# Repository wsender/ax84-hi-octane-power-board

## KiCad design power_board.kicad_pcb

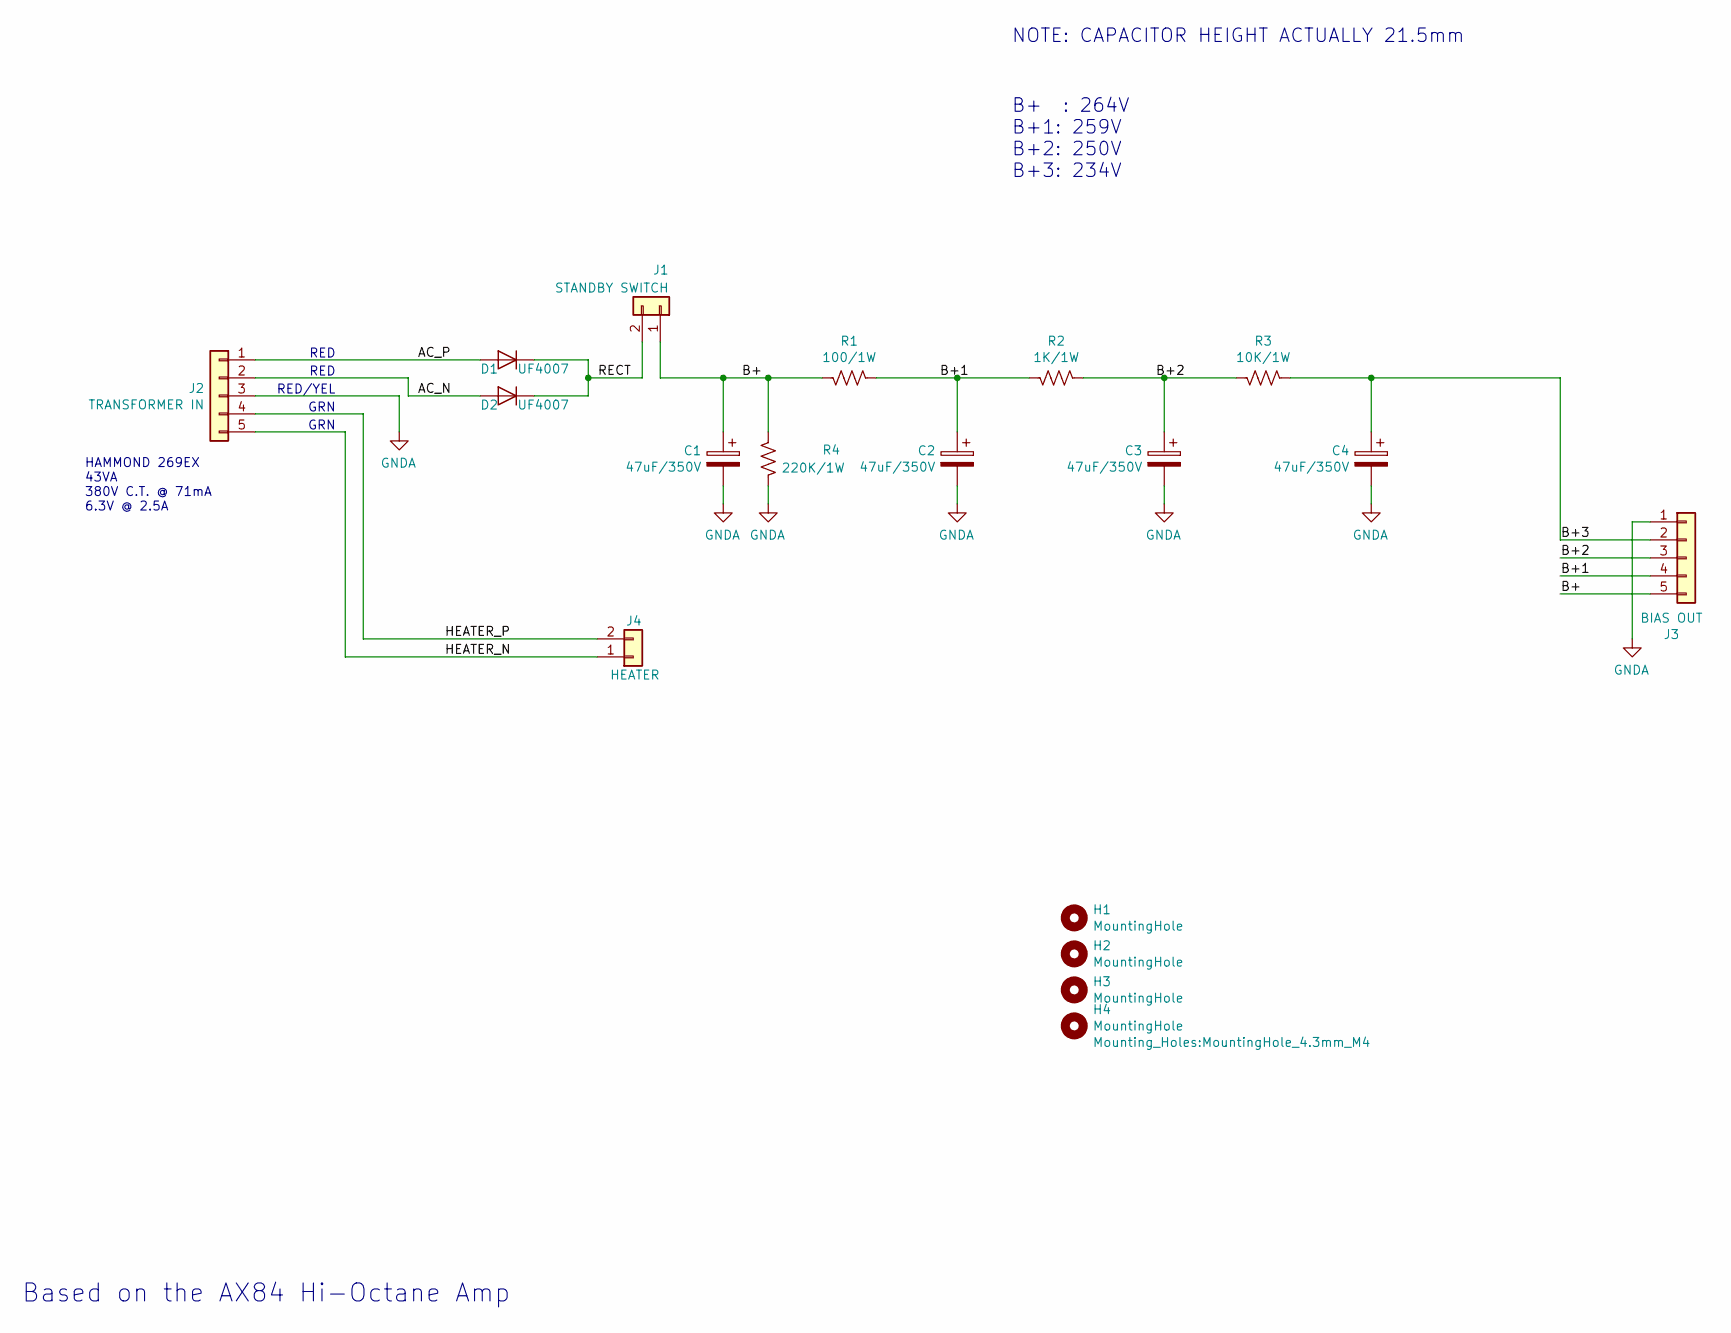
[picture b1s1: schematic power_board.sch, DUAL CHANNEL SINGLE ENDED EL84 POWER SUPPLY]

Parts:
C1, C2, C3, C4: 47uF/350V; CP_Radial_D16.0mm_P7.50mm; DIGIKEY PN 493-14944-ND
D1, D2: UF4007; D_DO-41_SOD81_P10.16mm_Horizontal; DIGIKEY PN UF4007-E3/54GICT-ND
H1, H2, H3, H4: MountingHole; MountingHole_4.3mm_M4
J1: STANDBY SWITCH; TerminalBlock_Pheonix_PT-3.5mm_2pol; DIGIKEY PN 277-6354-ND
J2: TRANSFORMER IN; TerminalBlock_Pheonix_PT-3.5mm_5pol; DIGIKEY PN 277-7675-ND
J3: BIAS OUT; TerminalBlock_Pheonix_PT-3.5mm_5pol; DIGIKEY PN 277-7675-ND
J4: HEATER; TerminalBlock_Pheonix_PT-3.5mm_2pol; DIGIKEY PN 277-6354-ND
R1: 100/1W; R_Axial_DIN0207_L6.3mm_D2.5mm_P10.16mm_Horizontal; DIGIKEY PN 100WCT-ND
R2: 1K/1W; R_Axial_DIN0207_L6.3mm_D2.5mm_P10.16mm_Horizontal; DIGIKEY PN 1KWCT-ND
R3: 10K/1W; R_Axial_DIN0207_L6.3mm_D2.5mm_P10.16mm_Horizontal; DIGIKEY PN 10KWCT-ND
R4: 220K/1W; R_Axial_DIN0207_L6.3mm_D2.5mm_P10.16mm_Horizontal; DIGIKEY PN 220KWCT-ND

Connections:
/AC_N: D2.2 (A), J2.2
/AC_P: D1.2 (A), J2.1
/B+: C1.1, J1.1, J3.5, R1.1, R4.1
/B+1: C2.1, J3.4, R1.2, R2.1
/B+2: C3.1, J3.3, R2.2, R3.1
/B+3: C4.1, J3.2, R3.2
/HEATER_N: J2.5, J4.1
/HEATER_P: J2.4, J4.2
/RECT: D1.1 (K), D2.1 (K), J1.2
GNDA: C1.2, C2.2, C3.2, C4.2, J2.3, J3.1, R4.2

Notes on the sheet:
Based on the AX84 Hi-Octane Amp
RED
RED/YEL
GRN
B+ : 264V B+1: 259V B+2: 250V B+3: 234V
NOTE: CAPACITOR HEIGHT ACTUALLY 21.5mm
HAMMOND 269EX 43VA 380V C.T. @ 71mA 6.3V @ 2.5A

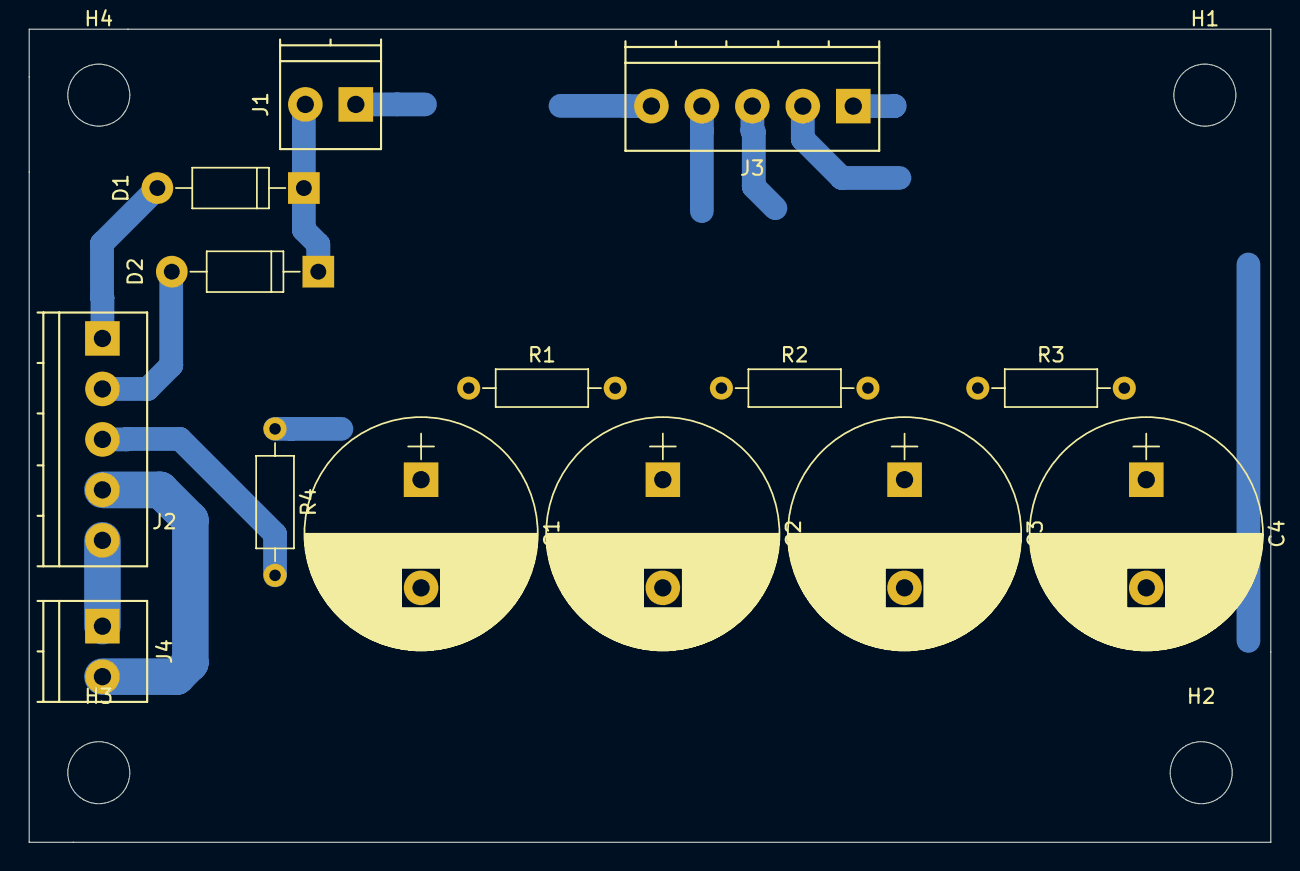
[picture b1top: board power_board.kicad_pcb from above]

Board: 2 copper layers, 86.1 x 56.4 mm, 18 parts (0 on the bottom side), 10 nets.

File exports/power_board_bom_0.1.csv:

Component,Description,Part,References,Value,Footprint,Quantity Per PCB,Datasheet,DIGIKEY PN
1,Polarized capacitor,CP,C1 C2 C3 C4,47uF/350V,CP_Radial_D16.0mm_P7.50mm,4,http://nichicon-us.com/english/products/pdfs/e-ucs.pdf,493-14944-ND
2,Diode,D,D1 D2,UF4007,D_DO-41_SOD81_P10.16mm_Horizontal,2,http://www.vishay.com/docs/88755/uf4001.pdf,UF4007-E3/54GICT-ND
3,"Generic connector, single row, 01x02, script generated (kicad-library-utils/schlib/autogen/connector/)",Conn_01x02,J1 J4,STANDBY SWITCH,TerminalBlock_Pheonix_PT-3.5mm_2pol,2,https://media.digikey.com/pdf/Data%20Sheets/Phoenix%20Contac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,277-1721-ND
4,"Generic connector, single row, 01x05, script generated (kicad-library-utils/schlib/autogen/connector/)",Conn_01x05,J2 J3,TRANSFORMER IN,TerminalBlock_Pheonix_PT-3.5mm_5pol,2,https://media.digikey.com/pdf/Data%20Sheets/Phoenix%20Contac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,277-1580-ND
5,"Resistor, US symbol",R_US,R1,100/1W,R_Axial_DIN0207_L6.3mm_D2.5mm_P10.16mm_Horizontal,1,http://www.yageo.com/documents/recent/Yageo%20LR_FMP_2013.pdf,100WCT-ND
6,"Resistor, US symbol",R_US,R3,10K/1W,R_Axial_DIN0207_L6.3mm_D2.5mm_P10.16mm_Horizontal,1,http://www.yageo.com/documents/recent/Yageo%20LR_FMP_2013.pdf,10KWCT-ND
7,"Resistor, US symbol",R_US,R2,1K/1W,R_Axial_DIN0207_L6.3mm_D2.5mm_P10.16mm_Horizontal,1,http://www.yageo.com/documents/recent/Yageo%20LR_FMP_2013.pdf,1KWCT-ND
8,"Resistor, US symbol",R_US,R4,220K/1W,R_Axial_DIN0207_L6.3mm_D2.5mm_P10.16mm_Horizontal,1,http://www.yageo.com/documents/recent/Yageo%20LR_FMP_2013.pdf,220KWCT-ND





Component Groups:,8
Component Count:,14
Fitted Components:,14
Number of PCBs:,1
Total components:,14
Schematic Version:,0.1
Schematic Date:,2019-05-04
BoM Date:,5/7/2019 9:29:05 PM
Schematic Source:,C:\Users\William\Dropbox\Engineering\Projects\Jack & Will Amp\Power Board\power_board\power_board.sch
KiCad Version:,Eeschema (5.1.2)-1

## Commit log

2019-05-08 initial commit of power board
2019-05-22 rev 0.2 updates
    corrected component pitch issue on connectors for BOM, made power pcb
    single sided routing, added aux origin for gerber
